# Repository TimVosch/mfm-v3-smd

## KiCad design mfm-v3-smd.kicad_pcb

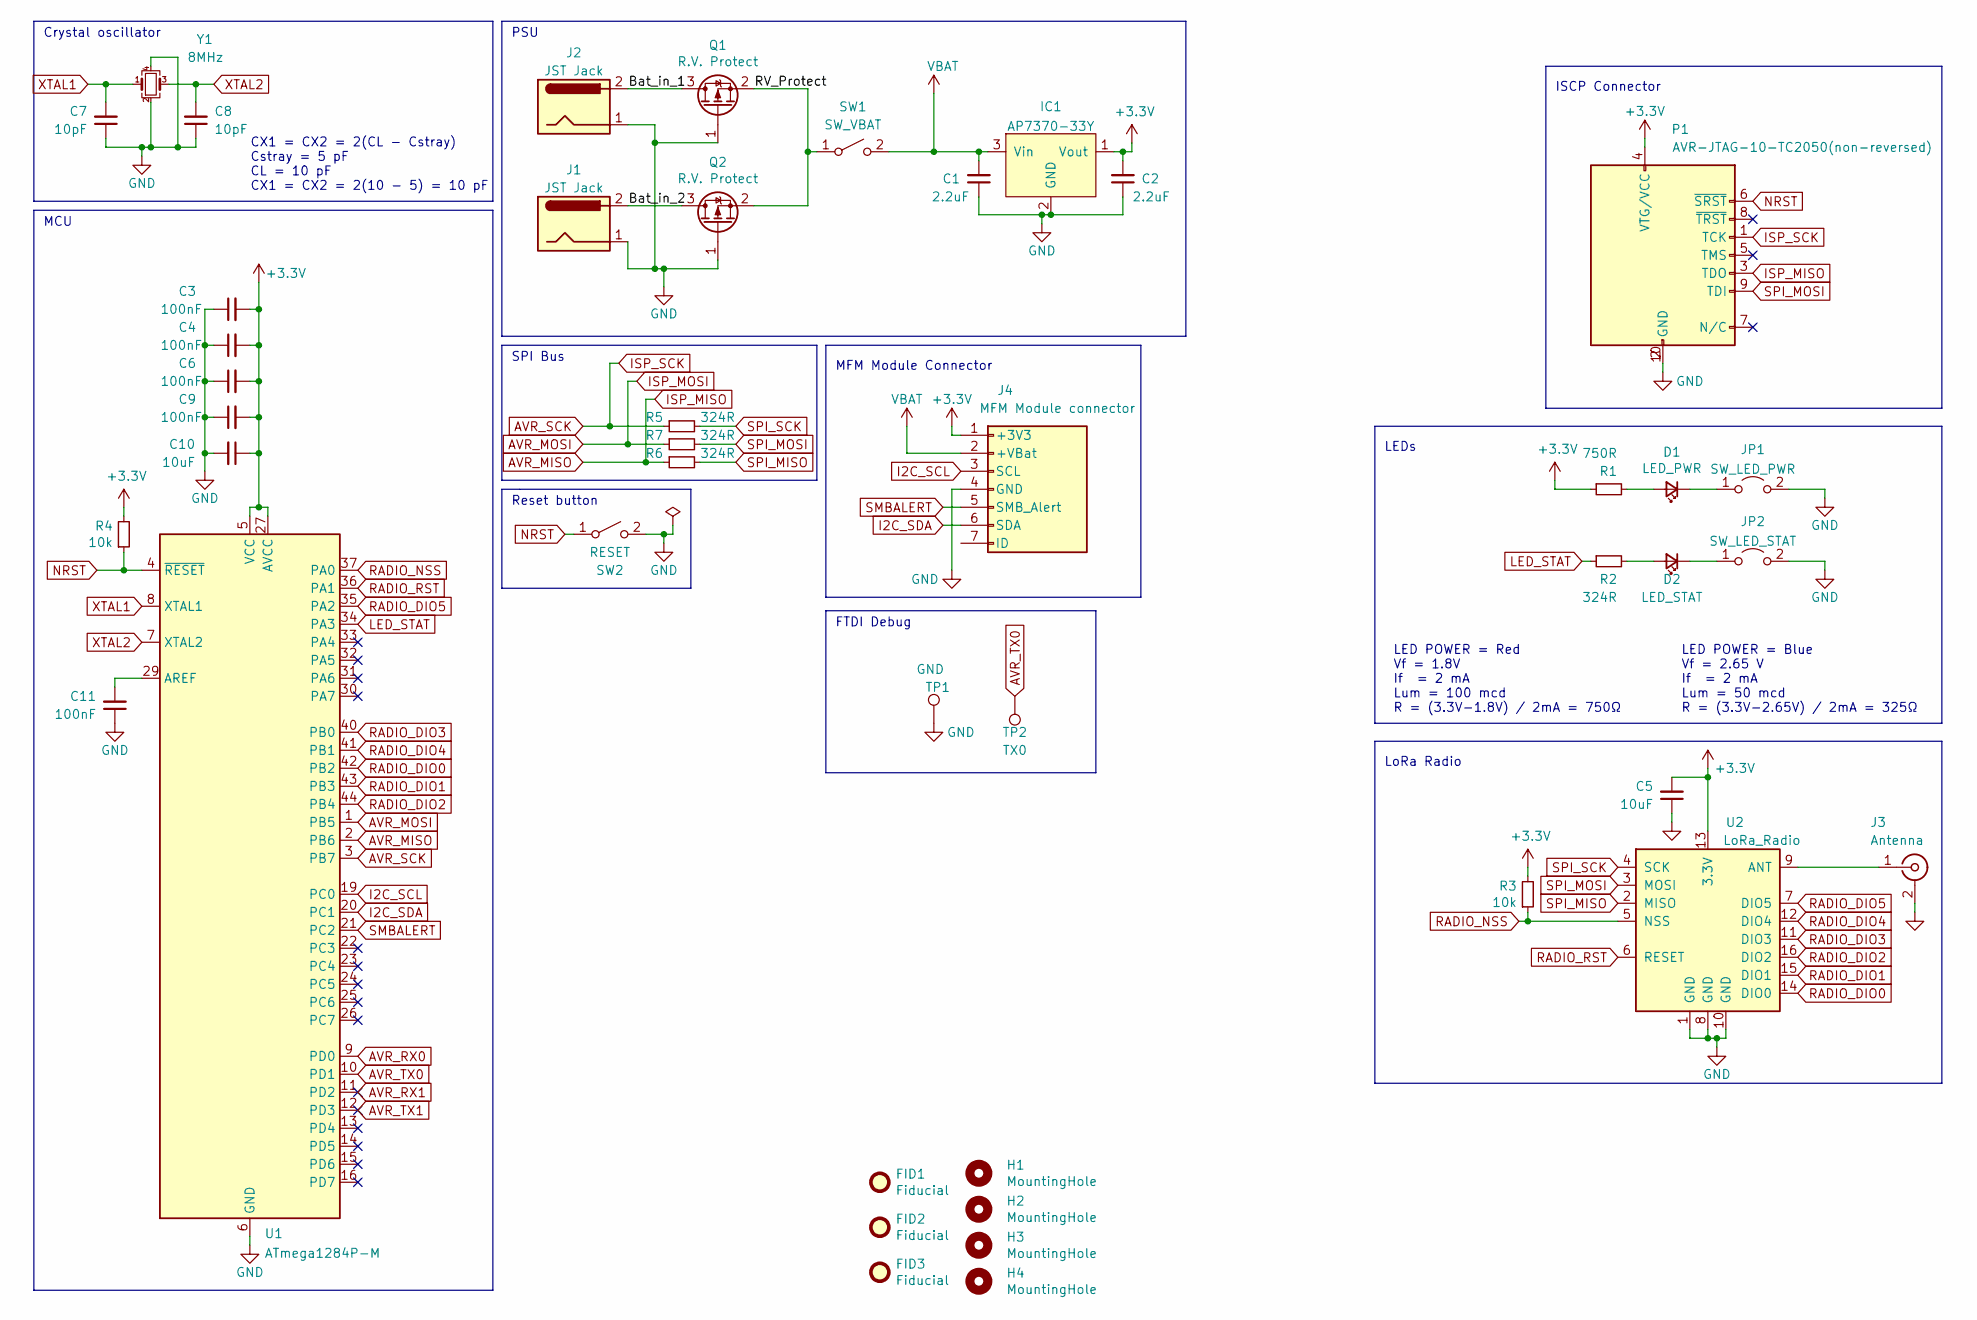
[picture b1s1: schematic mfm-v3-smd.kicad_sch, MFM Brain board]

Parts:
C1, C2: 2.2uF; C_0603_1608Metric; MFR# C1608X7R1A225K080AE; LCSC C23630
C3, C4, C6, C9, C11: 100nF; C_0603_1608Metric; MFR# C1608X7R1E104K080AA; LCSC C14663
C5, C10: 10uF; C_0805_2012Metric_GRM21BR61E106MA73L; MFR# GRM21BR61E106MA73L; LCSC C15850
C7, C8: 10pF; C_0603_1608Metric; MFR# GRT0335C1E100GA02D; LCSC C1648
D1: LED_PWR; LED_0805_2012Metric_APT2012LSECK; MFR# APT2012LSECK/J3-PRV; LCSC C84256
D2: LED_STAT; LED_0805_2012Metric_APTD2012LQBC-D; MFR# APTD2012LQBC/D; LCSC C2293
FID1, FID2, FID3: Fiducial; Fiducial_1mm_Mask2mm
H1, H2, H3, H4: MountingHole; MountingHole_2.7mm_M2.5_DIN965
IC1: AP7370-33Y; SOT-89-3
J1, J2: JST Jack; JST_PH_B2B-PH-SM4-TB_1x02-1MP_P2.00mm_Vertical
J3: Antenna; LINX_CONMHF1-SMD-G-T; MFR# CONSMA001-SMD-G-T
J4: MFM Module connector; JST_PH_B7B-PH-SM4-TB_1x07-1MP_P2.00mm_Vertical
JP1: SW_LED_PWR; SolderJumper-2_P1.3mm_Open_RoundedPad1.0x1.5mm
JP2: SW_LED_STAT; SolderJumper-2_P1.3mm_Open_RoundedPad1.0x1.5mm
P1: AVR-JTAG-10-TC2050(non-reversed); TC2050-IDC-NL
Q1, Q2: R.V. Protect; SOT-23; MFR# SI2315BDS-T1-E3; LCSC C10487
R1: 750R; R_0603_1608Metric_CRCW...C; MFR# CRCW0603750RFKEAC; LCSC C23241
R2, R5, R6, R7: 324R; R_0603_1608Metric_CRCW...C; MFR# CRCW0603324RFKEA; LCSC C227819
R3, R4: 10k; R_0603_1608Metric_CRCW...C; MFR# RCC060310K0FKEA; LCSC C25804
SW1: SW_VBAT; PinHeader_1x02_P2.54mm_Vertical; MFR# 800-10-002-10-002101; LCSC C160332
SW2: RESET; PTS815SJK250SMTRLFS; MFR# PTS636 SM43 SMTR LFS; LCSC C720477
TP1: GND; TestPoint_Pad_D1.5mm
TP2: TX0; TestPoint_Pad_D1.5mm
U1: ATmega1284P-M; QFN-44-1EP_7x7mm_P0.5mm_EP5.2x5.2mm
U2: LoRa_Radio; HOPERF_RFM9XW_SMD; MFR# SX1276-Module
Y1: 8MHz; Crystal_SMD_Abracon_ABM3B-4Pin_5.0x3.2mm; MFR# ABM3B-8.000MHZ-10-1-U-T; LCSC C254382

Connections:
+3V3: C2.2, C3.2, C4.2, C5.2, C6.2, C9.2, C10.1, IC1.1 (Vout), J4.1 (+3V3), P1.4 (VTG/VCC), R1.1, R3.2, R4.2, U1.5 (VCC), U1.17 (VCC), U1.27 (AVCC), U1.38 (VCC), U2.13 (3.3V)
/Bat_in_1: J2.2, Q1.3 (D)
/Bat_in_2: J1.2, Q2.3 (D)
AVR_MISO: P1.3 (TDO), R6.1, U1.2 (PB6)
AVR_MOSI: R7.1, U1.1 (PB5)
AVR_RX0: U1.9 (PD0)
AVR_RX1: U1.11 (PD2)
AVR_SCK: P1.1 (TCK), R5.1, U1.3 (PB7)
AVR_TX0: TP2.1, U1.10 (PD1)
AVR_TX1: U1.12 (PD3)
GND: C1.1, C2.1, C3.1, C4.1, C5.1, C6.1, C7.1, C8.1, C9.1, C10.2, C11.1, IC1.2 (GND), J1.1, J2.1, J3.2 (Ext), J4.4 (GND), JP1.2 (B), JP2.2 (B), P1.2 (GND), P1.10 (GND), Q1.1 (G), Q2.1 (G), SW2.2 (B), TP1.1, U1.6 (GND), U1.18 (GND), U1.28 (GND), U1.39 (GND), U1.45 (GND), U2.1 (GND), U2.8 (GND), U2.10 (GND), Y1.2, Y1.4
I2C_SCL: J4.3 (SCL), U1.19 (PC0)
I2C_SDA: J4.6 (SDA), U1.20 (PC1)
LED_STAT: R2.1, U1.34 (PA3)
NRST: P1.6 (~SRST), R4.1, SW2.1 (A), U1.4 (~RESET)
unnamed: C11.2, U1.29 (AREF)
unnamed: D1.1 (K), JP1.1 (A)
unnamed: D1.2 (A), R1.2
unnamed: D2.1 (K), JP2.1 (A)
unnamed: D2.2 (A), R2.2
unnamed: J3.1 (In), U2.9 (ANT)
unnamed: Q1.2 (S), Q2.2 (S), SW1.1 (A)
RADIO_DIO0: U1.42 (PB2), U2.14 (DIO0)
RADIO_DIO1: U1.43 (PB3), U2.15 (DIO1)
RADIO_DIO2: U1.44 (PB4), U2.16 (DIO2)
RADIO_DIO3: U1.40 (PB0), U2.11 (DIO3)
RADIO_DIO4: U1.41 (PB1), U2.12 (DIO4)
RADIO_DIO5: U1.35 (PA2), U2.7 (DIO5)
RADIO_NSS: R3.1, U1.37 (PA0), U2.5 (NSS)
RADIO_RST: U1.36 (PA1), U2.6 (RESET)
SMBALERT: J4.5 (SMB_Alert), U1.21 (PC2)
SPI_MISO: R6.2, U2.2 (MISO)
SPI_MOSI: P1.9 (TDI), R7.2, U2.3 (MOSI)
SPI_SCK: R5.2, U2.4 (SCK)
VBAT: C1.2, IC1.3 (Vin), J4.2 (+VBat), SW1.2 (B)
XTAL1: C7.2, U1.8 (XTAL1), Y1.1
XTAL2: C8.2, U1.7 (XTAL2), Y1.3

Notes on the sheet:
LED POWER = Blue Vf = 2.65 V If = 2 mA Lum = 50 mcd R = (3.3V-2.65V) / 2mA = 325Ω
LEDs
SPI Bus
LoRa Radio
Crystal oscillator
ISCP Connector
CX1 = CX2 = 2(CL - Cstray) Cstray = 5 pF CL = 10 pF CX1 = CX2 = 2(10 - 5) = 10 pF
PSU
Reset button
FTDI Debug
LED POWER = Red Vf = 1.8V If = 2 mA Lum = 100 mcd R = (3.3V-1.8V) / 2mA = 750Ω
MFM Module Connector
MCU

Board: 2 copper layers, 44 parts (0 on the bottom side), 34 nets, no tracks yet.

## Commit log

2022-03-21 initial setup of v3.7
